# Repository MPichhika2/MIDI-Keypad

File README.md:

A MIDI-Keyboard

For this project, I designed a custom MIDI keypad PCB inspired by the MIDI Keypad project. The goal was to create a compact, customizable music controller that can send MIDI inputs to a computer using touch-sensitive keys, a rotary encoder, and a slide potentiometer.

The main components include a Seeed Studio XIAO ESP32-S3, seven capacitive touch pads, three SK6812 MINI-E RGB LEDs, an EC11 rotary encoder, and a Bourns slide potentiometer. As seen in my schematic view! 

I started by creating the circuit schematic in KiCad, assigning GPIO pins to the touch keys, LEDs, encoder, and slider. I connected the power and ground nets, added power flags, and fixed electrical rule errors.

Next, I assigned component footprints and created a custom footprint containing seven copper touch pads. I transferred everything into the PCB Editor, arranged the components, created the board outline, and routed the electrical connections using front and back copper layers.

I also modified the LED footprints for front mounting, corrected silkscreen issues, and added a ground plane with a keepout underneath the capacitive touch pads.

Finally, I checked the design using KiCad's Design Rules Checker, achieving zero electrical errors and zero unconnected items. I also began customizing the PCB with rounded corners and planned music-themed artwork and personalized lettering.

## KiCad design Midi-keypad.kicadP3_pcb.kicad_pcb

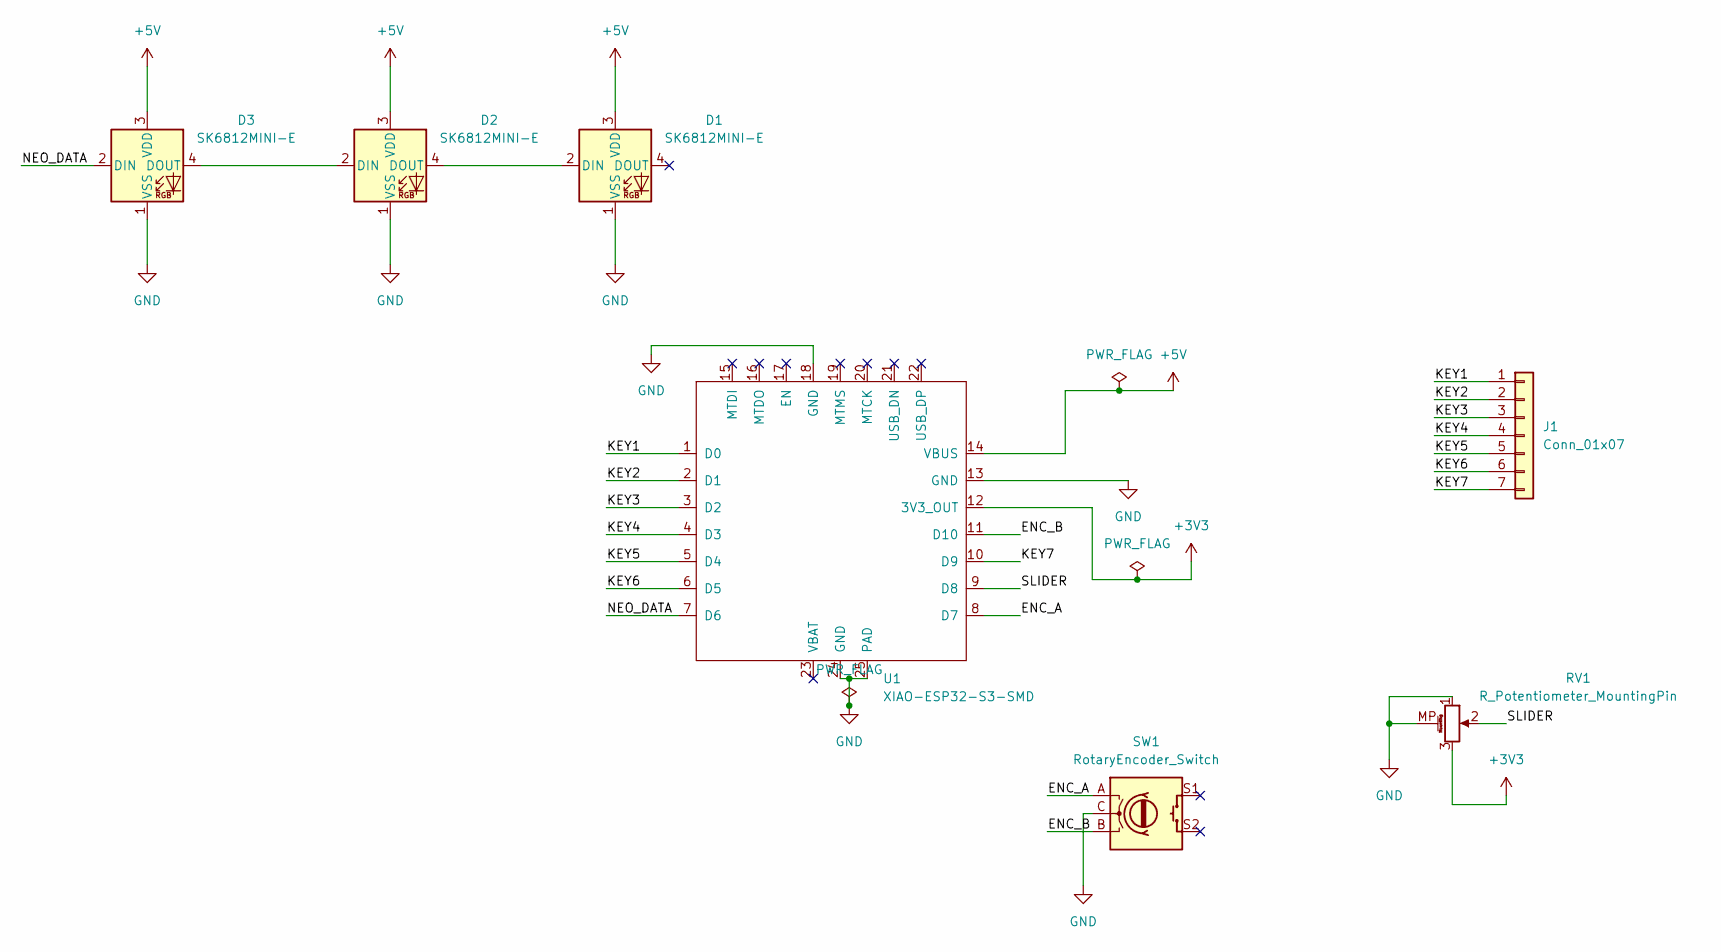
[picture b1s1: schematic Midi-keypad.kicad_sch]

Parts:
D1, D2, D3: SK6812MINI-E; SK6812_FrontMount
J1: Conn_01x07; KeyPads
RV1: R_Potentiometer_MountingPin; Potentiometer_Bourns_PTA3043_Single_Slide
SW1: RotaryEncoder_Switch; RotaryEncoder_Alps_EC11E-Switch_Vertical_H20mm
U1: XIAO-ESP32-S3-SMD

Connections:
+3V3: RV1.3, U1.12 (3V3_OUT)
+5V: D1.3 (VDD), D2.3 (VDD), D3.3 (VDD), U1.14 (VBUS)
/ENC_A: SW1.A, U1.8 (D7)
/ENC_B: SW1.B, U1.11 (D10)
/KEY1: J1.1, U1.1 (D0)
/KEY2: J1.2, U1.2 (D1)
/KEY3: J1.3, U1.3 (D2)
/KEY4: J1.4, U1.4 (D3)
/KEY5: J1.5, U1.5 (D4)
/KEY6: J1.6, U1.6 (D5)
/KEY7: J1.7, U1.10 (D9)
/NEO_DATA: D3.2 (DIN), U1.7 (D6)
/SLIDER: RV1.2, U1.9 (D8)
GND: D1.1 (VSS), D2.1 (VSS), D3.1 (VSS), RV1.1, RV1.MP (MountPin), SW1.C, U1.13 (GND), U1.18 (GND), U1.24 (GND), U1.25 (PAD)
unnamed: D1.2 (DIN), D2.4 (DOUT)
unnamed: D2.2 (DIN), D3.4 (DOUT)

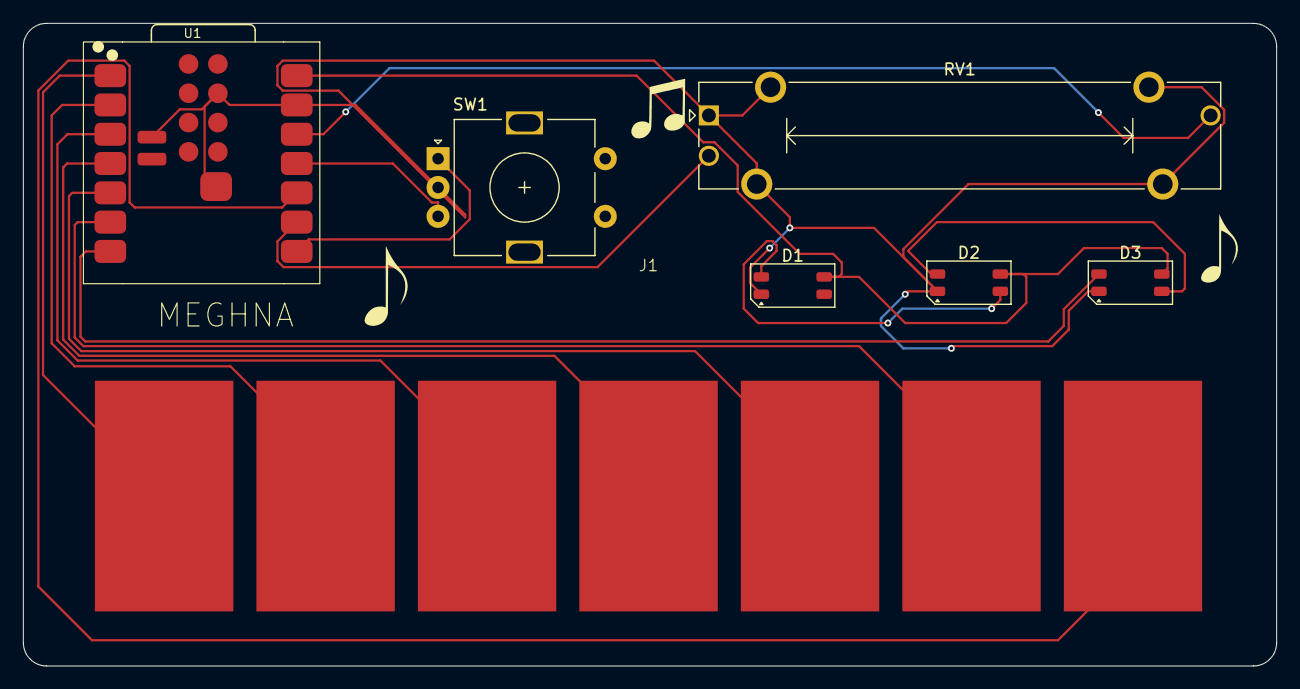
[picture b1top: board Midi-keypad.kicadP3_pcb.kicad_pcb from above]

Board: 2 copper layers, 108.7 x 55.7 mm, 7 parts (0 on the bottom side), 16 nets.
